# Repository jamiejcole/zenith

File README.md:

# Zenith
An open source EOS controller based on [ETC Lighthack](https://github.com/ETCLabs/lighthack).
I built this to assist with lighting programming alongside an ETC Element 2, more specifically out of my hatred for solely using point-and-click to control my moving heads. Hopefully this project is of use to someone else too.

## Features
- 3 customisable rotary encoders (default to pan, tilt and zoom)
- 3 cherry MX blue switches to change the action of the corresponding encoder
- Go and stop/back cue buttons
- OLED screen showing current encoder settings and values

## Hardware
To build this, I used:
- 5x cherry MX blue switches
- 3x rotary encoders with pushbuttons
- 0.96 128x64 OLED screen
- Arduino UNO clone
- 3D printed housing and encoder wheels
- 4x M3 threaded inserts

## Notable challenges
Due to using an Arduino clone rather than a genuine one, the arduino had trouble communicating to the Element 2 via OSC over USB, which was a headache to troubleshoot. 
This was mitigated by exiting EOS and using a dodgy workaround to get to control panel and sideloading the Arduino serial drivers by using a USB drive. The comments section of [Nathan Butler's Lighthack](https://tinkering.home.blog/2019/02/19/lighthack-usb-encoder-wing-for-etc-element/) project helped significantly through the process of attempting to get this to work:

>> A couple of things to try:
– The usual driver for the knockoff arduino’s that I’ve used was available at https://learn.sparkfun.com/tutorials/how-to-install-ch340-drivers/all#drivers-if-you-need-them. I downloaded the windows driver from there, put it on a USB, logged into the desk in admin mode, and was able to open the USB drive and just install it.
– Similarly, you could try installing the Arduino software on the ETC desk too, which includes some drivers as part of it’s install.
– Whilst I’m guessing that you’re using the same USB cable at the desk as you did to upload the firmware to the arduino, just in case you are not, try a different USB cable. I have had some funny issues which turned out to be an intermittently faulty cable
Hope that helps!

>> Element 2 CH340 Driver install
> Any update on this? I have a win7 element 2 console and my arduino uno clone is not being recognised at all in diagnostics page. It's using the CH340 chipset, really struggling to get this to work. Is there any way i can install the drivers onto the console?

Update on this, was able to install the correct drivers by:
- loading into the console ECU,
- spamming shift to open the sticky keys menu
- clicking the hyperlink on the prompt to open control panel
- open device manager from control panel
- find the COM port for the Arduino 
- insert usb with extracted .zip folder for windows 7 CH340 drivers, downloaded from [this page](https://www.wch-ic.com/downloads/CH341SER_ZIP.html)
- click update drivers 
- select update from local file
- find extracted driver folder on USB
- install drivers
- exit out of all windows and launch EOS primary
- COM4 port is now recognised and can talk to Arduino via OSC over USB

## Wiring
Here was my 'circuit diagram' for the build.

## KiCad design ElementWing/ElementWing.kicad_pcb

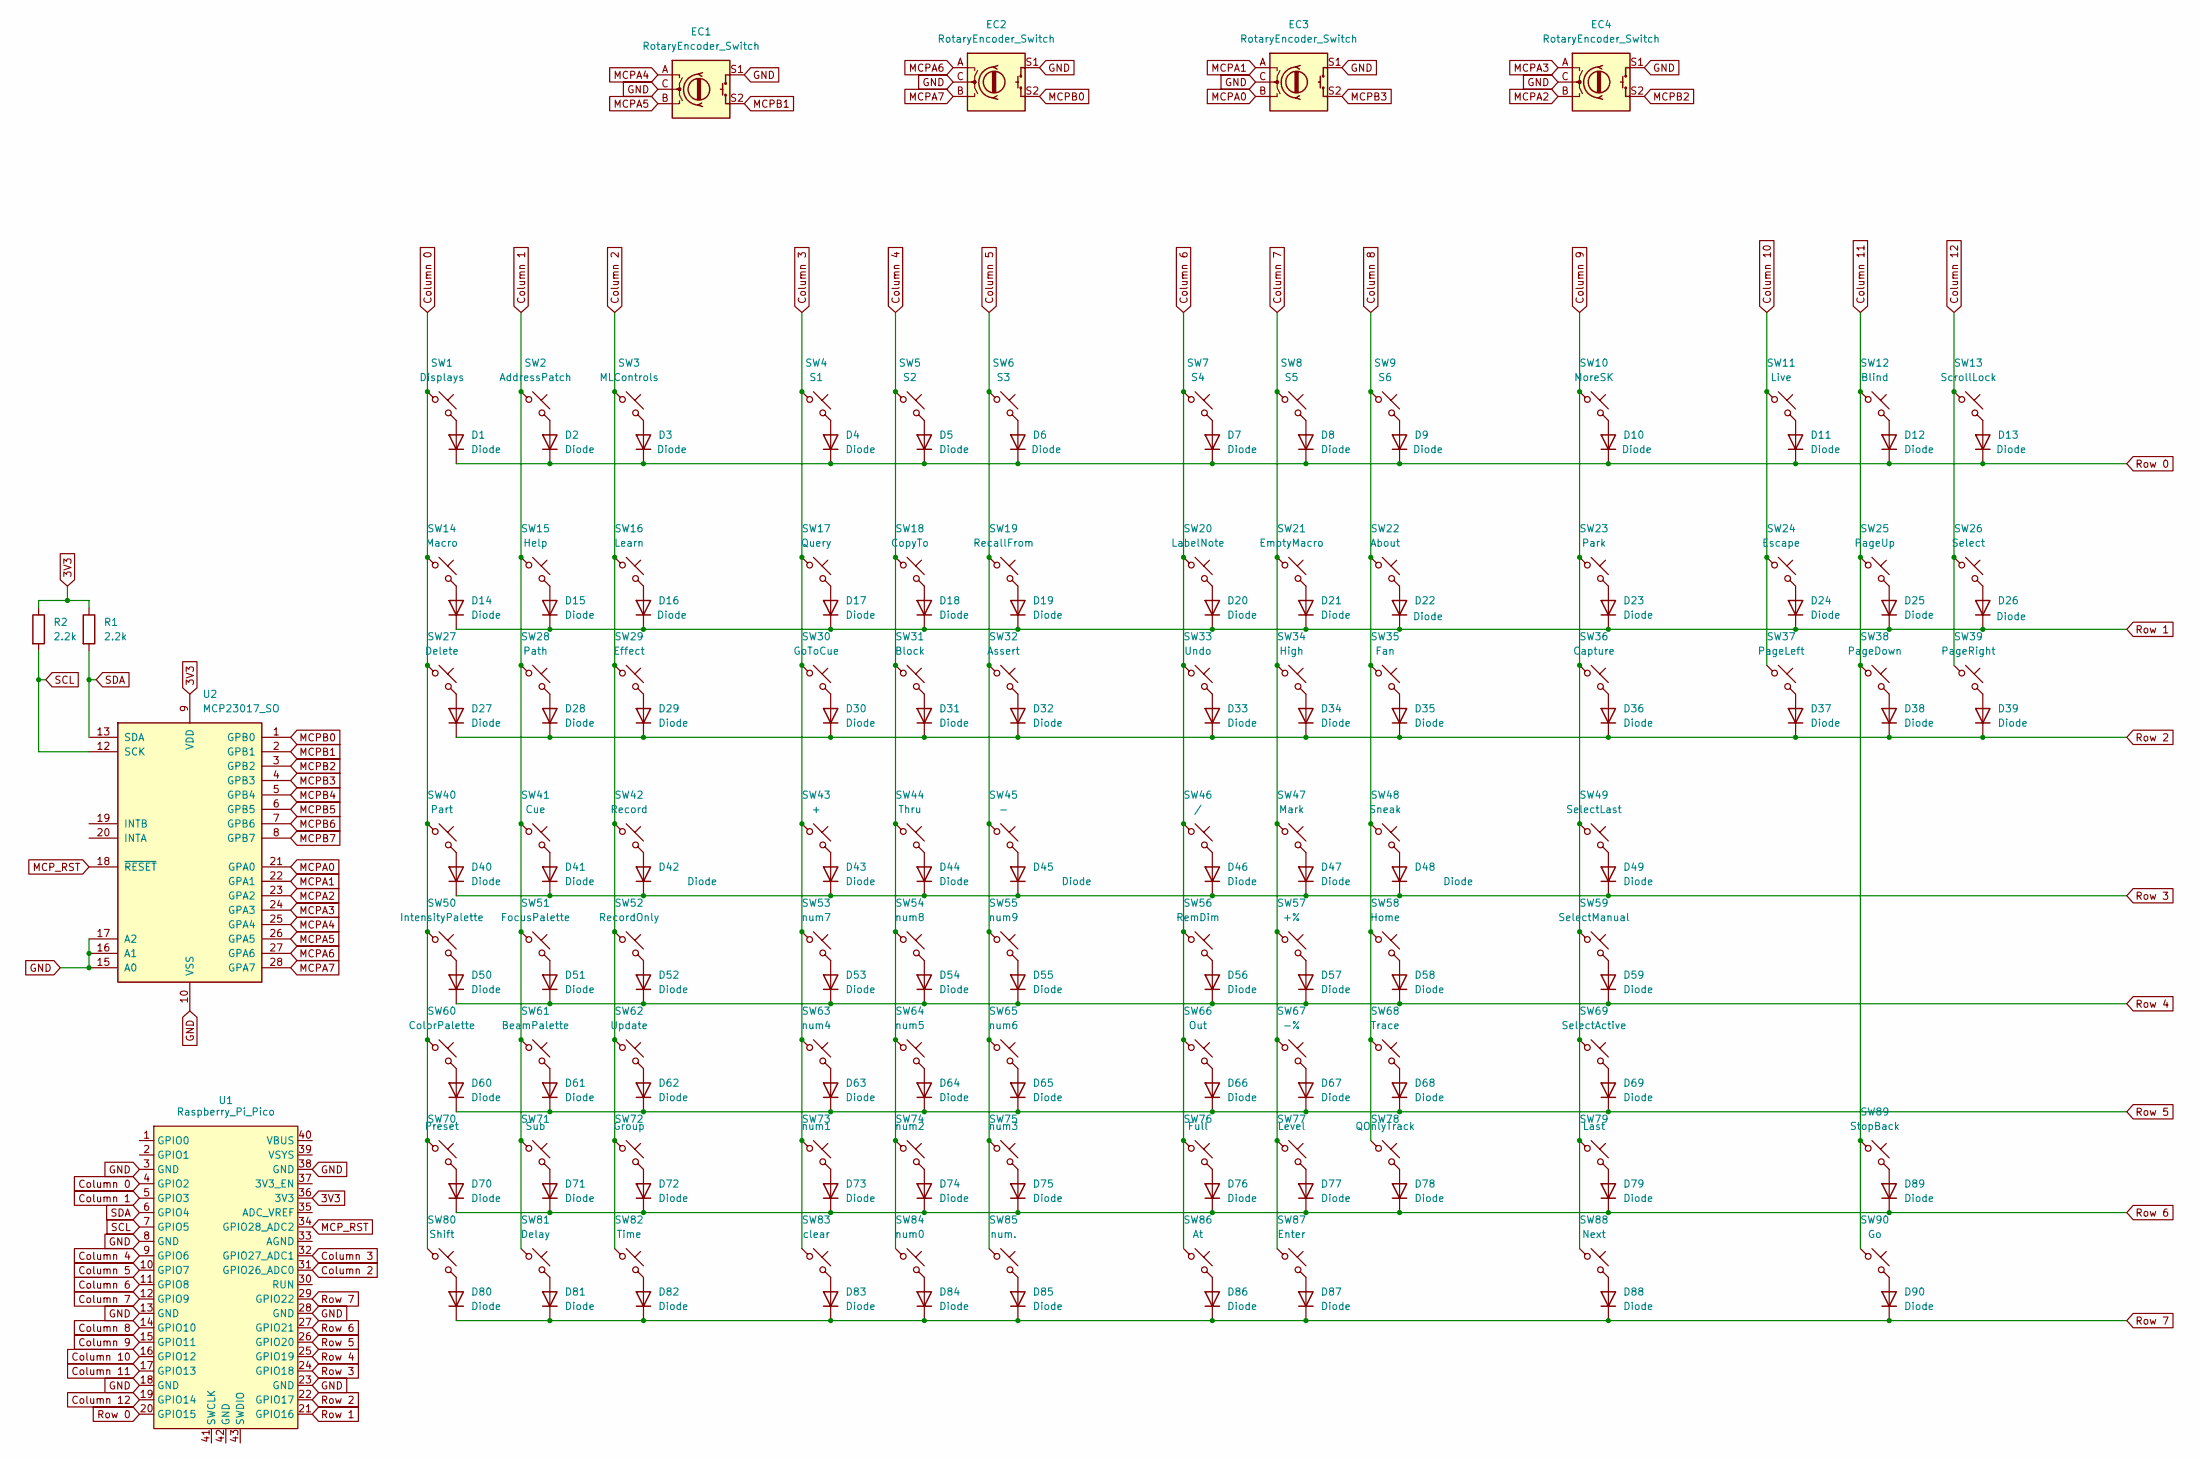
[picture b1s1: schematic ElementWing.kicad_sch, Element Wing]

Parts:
D1, D2, D3, D4, D5, D6, D7, D8, D9, D10, D11, D12, D13, D14, D15, D16, D17, D18, D19, D20, D21, D22, D23, D24, D25, D26, D27, D28, D29, D30, D31, D32, D33, D34, D35, D36, D37, D38, D39, D40, D41, D42, D43, D44, D45, D46, D47, D48, D49, D50, D51, D52, D53, D54, D55, D56, D57, D58, D59, D60, D61, D62, D63, D64, D65, D66, D67, D68, D69, D70, D71, D72, D73, D74, D75, D76, D77, D78, D79, D80, D81, D82, D83, D84, D85, D86, D87, D88, D89, D90: Diode; Diode_DO-35
EC1, EC2, EC3, EC4: RotaryEncoder_Switch; RotaryEncoder_Alps_EC11E-Switch_Vertical_H20mm
R1, R2: 2.2k; R_Axial_DIN0207_L6.3mm_D2.5mm_P10.16mm_Horizontal
SW1: Displays; MX_PCB_1.00u
SW2: AddressPatch; MX_PCB_1.00u
SW3: MLControls; MX_PCB_1.00u
SW4: S1; MX_PCB_1.00u
SW5: S2; MX_PCB_1.00u
SW6: S3; MX_PCB_1.00u
SW7: S4; MX_PCB_1.00u
SW8: S5; MX_PCB_1.00u
SW9: S6; MX_PCB_1.00u
SW10: MoreSK; MX_PCB_1.00u
SW11: Live; MX_PCB_1.00u
SW12: Blind; MX_PCB_1.00u
SW13: ScrollLock; MX_PCB_1.00u
SW14: Macro; MX_PCB_1.00u
SW15: Help; MX_PCB_1.00u
SW16: Learn; MX_PCB_1.00u
SW17: Query; MX_PCB_1.00u
SW18: CopyTo; MX_PCB_1.00u
SW19: RecallFrom; MX_PCB_1.00u
SW20: LabelNote; MX_PCB_1.00u
SW21: EmptyMacro; MX_PCB_1.00u
SW22: About; MX_PCB_1.00u
SW23: Park; MX_PCB_1.00u
SW24: Escape; MX_PCB_1.00u
SW25: PageUp; MX_PCB_1.00u
SW26: Select; MX_PCB_1.00u
SW27: Delete; MX_PCB_1.00u
SW28: Path; MX_PCB_1.00u
SW29: Effect; MX_PCB_1.00u
SW30: GoToCue; MX_PCB_1.00u
SW31: Block; MX_PCB_1.00u
SW32: Assert; MX_PCB_1.00u
SW33: Undo; MX_PCB_1.00u
SW34: High; MX_PCB_1.00u
SW35: Fan; MX_PCB_1.00u
SW36: Capture; MX_PCB_1.00u
SW37: PageLeft; MX_PCB_1.00u
SW38: PageDown; MX_PCB_1.00u
SW39: PageRight; MX_PCB_1.00u
SW40: Part; MX_PCB_1.00u
SW41: Cue; MX_PCB_1.00u
SW42: Record; MX_PCB_1.00u
SW43: +; MX_PCB_1.00u
SW44: Thru; MX_PCB_1.00u
SW45: -; MX_PCB_1.00u
SW46: /; MX_PCB_1.00u
SW47: Mark; MX_PCB_1.00u
SW48: Sneak; MX_PCB_1.00u
SW49: SelectLast; MX_PCB_1.00u
SW50: IntensityPalette; MX_PCB_1.00u
SW51: FocusPalette; MX_PCB_1.00u
SW52: RecordOnly; MX_PCB_1.00u
SW53: num7; MX_PCB_1.00u
SW54: num8; MX_PCB_1.00u
SW55: num9; MX_PCB_1.00u
SW56: RemDim; MX_PCB_1.00u
SW57: +%; MX_PCB_1.00u
SW58: Home; MX_PCB_1.00u
SW59: SelectManual; MX_PCB_1.00u
SW60: ColorPalette; MX_PCB_1.00u
SW61: BeamPalette; MX_PCB_1.00u
SW62: Update; MX_PCB_1.00u
SW63: num4; MX_PCB_1.00u
SW64: num5; MX_PCB_1.00u
SW65: num6; MX_PCB_1.00u
SW66: Out; MX_PCB_1.00u
SW67: -%; MX_PCB_1.00u
SW68: Trace; MX_PCB_1.00u
SW69: SelectActive; MX_PCB_1.00u
SW70: Preset; MX_PCB_1.00u
SW71: Sub; MX_PCB_1.00u
SW72: Group; MX_PCB_1.00u
SW73: num1; MX_PCB_1.00u
SW74: num2; MX_PCB_1.00u
SW75: num3; MX_PCB_1.00u
SW76: Full; MX_PCB_1.00u
SW77: Level; MX_PCB_1.00u
SW78: QOnlyTrack; MX_PCB_1.00u
SW79: Last; MX_PCB_1.00u
SW80: Shift; MX_PCB_1.00u
SW81: Delay; MX_PCB_1.00u
SW82: Time; MX_PCB_1.00u
SW83: clear; MX_PCB_1.00u
SW84: num0; MX_PCB_1.00u
SW85: num.; MX_PCB_1.00u
SW86: At; MX_PCB_1.00u
SW87: Enter; MX_PCB_1.00u
SW88: Next; MX_PCB_1.00u
SW89: StopBack; MX_PCB_1.00u
SW90: Go; MX_PCB_1.00u
U1: Raspberry_Pi_Pico
U2: MCP23017_SO; SOIC-28W_7.5x17.9mm_P1.27mm

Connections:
3V3: R1.1, R2.1, U1.36 (3V3), U2.9 (VDD)
Column 0: SW1.1, SW14.1, SW27.1, SW40.1, SW50.1, SW60.1, SW70.1, SW80.1, U1.4 (GPIO2)
Column 1: SW2.1, SW15.1, SW28.1, SW41.1, SW51.1, SW61.1, SW71.1, SW81.1, U1.5 (GPIO3)
Column 2: SW3.1, SW16.1, SW29.1, SW42.1, SW52.1, SW62.1, SW72.1, SW82.1, U1.31 (GPIO26_ADC0)
Column 3: SW4.1, SW17.1, SW30.1, SW43.1, SW53.1, SW63.1, SW73.1, SW83.1, U1.32 (GPIO27_ADC1)
Column 4: SW5.1, SW18.1, SW31.1, SW44.1, SW54.1, SW64.1, SW74.1, SW84.1, U1.9 (GPIO6)
Column 5: SW6.1, SW19.1, SW32.1, SW45.1, SW55.1, SW65.1, SW75.1, SW85.1, U1.10 (GPIO7)
Column 6: SW7.1, SW20.1, SW33.1, SW46.1, SW56.1, SW66.1, SW76.1, SW86.1, U1.11 (GPIO8)
Column 7: SW8.1, SW21.1, SW34.1, SW47.1, SW57.1, SW67.1, SW77.1, SW87.1, U1.12 (GPIO9)
Column 8: SW9.1, SW22.1, SW35.1, SW48.1, SW58.1, SW68.1, SW78.1, U1.14 (GPIO10)
Column 9: SW10.1, SW23.1, SW36.1, SW49.1, SW59.1, SW69.1, SW79.1, SW88.1, U1.15 (GPIO11)
Column 10: SW11.1, SW24.1, SW37.1, U1.16 (GPIO12)
Column 11: SW12.1, SW25.1, SW38.1, SW89.1, SW90.1, U1.17 (GPIO13)
Column 12: SW13.1, SW26.1, SW39.1, U1.19 (GPIO14)
GND: EC1.C, EC1.S1, EC2.C, EC2.S1, EC3.C, EC3.S1, EC4.C, EC4.S1, U1.3 (GND), U1.8 (GND), U1.13 (GND), U1.18 (GND), U1.23 (GND), U1.28 (GND), U1.38 (GND), U2.10 (VSS), U2.15 (A0), U2.16 (A1), U2.17 (A2)
MCPA0: EC3.B, U2.21 (GPA0)
MCPA1: EC3.A, U2.22 (GPA1)
MCPA2: EC4.B, U2.23 (GPA2)
MCPA3: EC4.A, U2.24 (GPA3)
MCPA4: EC1.A, U2.25 (GPA4)
MCPA5: EC1.B, U2.26 (GPA5)
MCPA6: EC2.A, U2.27 (GPA6)
MCPA7: EC2.B, U2.28 (GPA7)
MCPB0: EC2.S2, U2.1 (GPB0)
MCPB1: EC1.S2, U2.2 (GPB1)
MCPB2: EC4.S2, U2.3 (GPB2)
MCPB3: EC3.S2, U2.4 (GPB3)
MCPB4: U2.5 (GPB4)
MCPB5: U2.6 (GPB5)
MCPB6: U2.7 (GPB6)
MCPB7: U2.8 (GPB7)
MCP_RST: U1.34 (GPIO28_ADC2), U2.18 (~RESET)
unnamed: D1.2 (A), SW1.2
unnamed: D2.2 (A), SW2.2
unnamed: D3.2 (A), SW3.2
unnamed: D4.2 (A), SW4.2
unnamed: D5.2 (A), SW5.2
unnamed: D6.2 (A), SW6.2
unnamed: D7.2 (A), SW7.2
unnamed: D8.2 (A), SW8.2
unnamed: D9.2 (A), SW9.2
unnamed: D10.2 (A), SW10.2
unnamed: D11.2 (A), SW11.2
unnamed: D12.2 (A), SW12.2
unnamed: D13.2 (A), SW13.2
unnamed: D14.2 (A), SW14.2
unnamed: D15.2 (A), SW15.2
unnamed: D16.2 (A), SW16.2
unnamed: D17.2 (A), SW17.2
unnamed: D18.2 (A), SW18.2
unnamed: D19.2 (A), SW19.2
unnamed: D20.2 (A), SW20.2
unnamed: D21.2 (A), SW21.2
unnamed: D22.2 (A), SW22.2
unnamed: D23.2 (A), SW23.2
unnamed: D24.2 (A), SW24.2
unnamed: D25.2 (A), SW25.2
unnamed: D26.2 (A), SW26.2
unnamed: D27.2 (A), SW27.2
unnamed: D28.2 (A), SW28.2
unnamed: D29.2 (A), SW29.2
unnamed: D30.2 (A), SW30.2
unnamed: D31.2 (A), SW31.2
unnamed: D32.2 (A), SW32.2
unnamed: D33.2 (A), SW33.2
unnamed: D34.2 (A), SW34.2
unnamed: D35.2 (A), SW35.2
unnamed: D36.2 (A), SW36.2
unnamed: D37.2 (A), SW37.2
unnamed: D38.2 (A), SW38.2
unnamed: D39.2 (A), SW39.2
unnamed: D40.2 (A), SW40.2
unnamed: D41.2 (A), SW41.2
unnamed: D42.2 (A), SW42.2
unnamed: D43.2 (A), SW43.2
unnamed: D44.2 (A), SW44.2
unnamed: D45.2 (A), SW45.2
unnamed: D46.2 (A), SW46.2
unnamed: D47.2 (A), SW47.2
unnamed: D48.2 (A), SW48.2
unnamed: D49.2 (A), SW49.2
unnamed: D50.2 (A), SW50.2
unnamed: D51.2 (A), SW51.2
unnamed: D52.2 (A), SW52.2
unnamed: D53.2 (A), SW53.2
unnamed: D54.2 (A), SW54.2
unnamed: D55.2 (A), SW55.2
unnamed: D56.2 (A), SW56.2
unnamed: D57.2 (A), SW57.2
unnamed: D58.2 (A), SW58.2
unnamed: D59.2 (A), SW59.2
unnamed: D60.2 (A), SW60.2
unnamed: D61.2 (A), SW61.2
unnamed: D62.2 (A), SW62.2
unnamed: D63.2 (A), SW63.2
unnamed: D64.2 (A), SW64.2
unnamed: D65.2 (A), SW65.2
unnamed: D66.2 (A), SW66.2
unnamed: D67.2 (A), SW67.2
unnamed: D68.2 (A), SW68.2
unnamed: D69.2 (A), SW69.2
unnamed: D70.2 (A), SW70.2
unnamed: D71.2 (A), SW71.2
unnamed: D72.2 (A), SW72.2
unnamed: D73.2 (A), SW73.2
unnamed: D74.2 (A), SW74.2
unnamed: D75.2 (A), SW75.2
unnamed: D76.2 (A), SW76.2
unnamed: D77.2 (A), SW77.2
unnamed: D78.2 (A), SW78.2
unnamed: D79.2 (A), SW79.2
unnamed: D80.2 (A), SW80.2
unnamed: D81.2 (A), SW81.2
unnamed: D82.2 (A), SW82.2
unnamed: D83.2 (A), SW83.2
unnamed: D84.2 (A), SW84.2
unnamed: D85.2 (A), SW85.2
unnamed: D86.2 (A), SW86.2
unnamed: D87.2 (A), SW87.2
unnamed: D88.2 (A), SW88.2
unnamed: D89.2 (A), SW89.2
unnamed: D90.2 (A), SW90.2
Row 0: D1.1 (K), D2.1 (K), D3.1 (K), D4.1 (K), D5.1 (K), D6.1 (K), D7.1 (K), D8.1 (K), D9.1 (K), D10.1 (K), D11.1 (K), D12.1 (K), D13.1 (K), U1.20 (GPIO15)
Row 1: D14.1 (K), D15.1 (K), D16.1 (K), D17.1 (K), D18.1 (K), D19.1 (K), D20.1 (K), D21.1 (K), D22.1 (K), D23.1 (K), D24.1 (K), D25.1 (K), D26.1 (K), U1.21 (GPIO16)
Row 2: D27.1 (K), D28.1 (K), D29.1 (K), D30.1 (K), D31.1 (K), D32.1 (K), D33.1 (K), D34.1 (K), D35.1 (K), D36.1 (K), D37.1 (K), D38.1 (K), D39.1 (K), U1.22 (GPIO17)
Row 3: D40.1 (K), D41.1 (K), D42.1 (K), D43.1 (K), D44.1 (K), D45.1 (K), D46.1 (K), D47.1 (K), D48.1 (K), D49.1 (K), U1.24 (GPIO18)
Row 4: D50.1 (K), D51.1 (K), D52.1 (K), D53.1 (K), D54.1 (K), D55.1 (K), D56.1 (K), D57.1 (K), D58.1 (K), D59.1 (K), U1.25 (GPIO19)
Row 5: D60.1 (K), D61.1 (K), D62.1 (K), D63.1 (K), D64.1 (K), D65.1 (K), D66.1 (K), D67.1 (K), D68.1 (K), D69.1 (K), U1.26 (GPIO20)
Row 6: D70.1 (K), D71.1 (K), D72.1 (K), D73.1 (K), D74.1 (K), D75.1 (K), D76.1 (K), D77.1 (K), D78.1 (K), D79.1 (K), D89.1 (K), U1.27 (GPIO21)
Row 7: D80.1 (K), D81.1 (K), D82.1 (K), D83.1 (K), D84.1 (K), D85.1 (K), D86.1 (K), D87.1 (K), D88.1 (K), D90.1 (K), U1.29 (GPIO22)
SCL: R2.2, U1.7 (GPIO5), U2.12 (SCK)
SDA: R1.2, U1.6 (GPIO4), U2.13 (SDA)

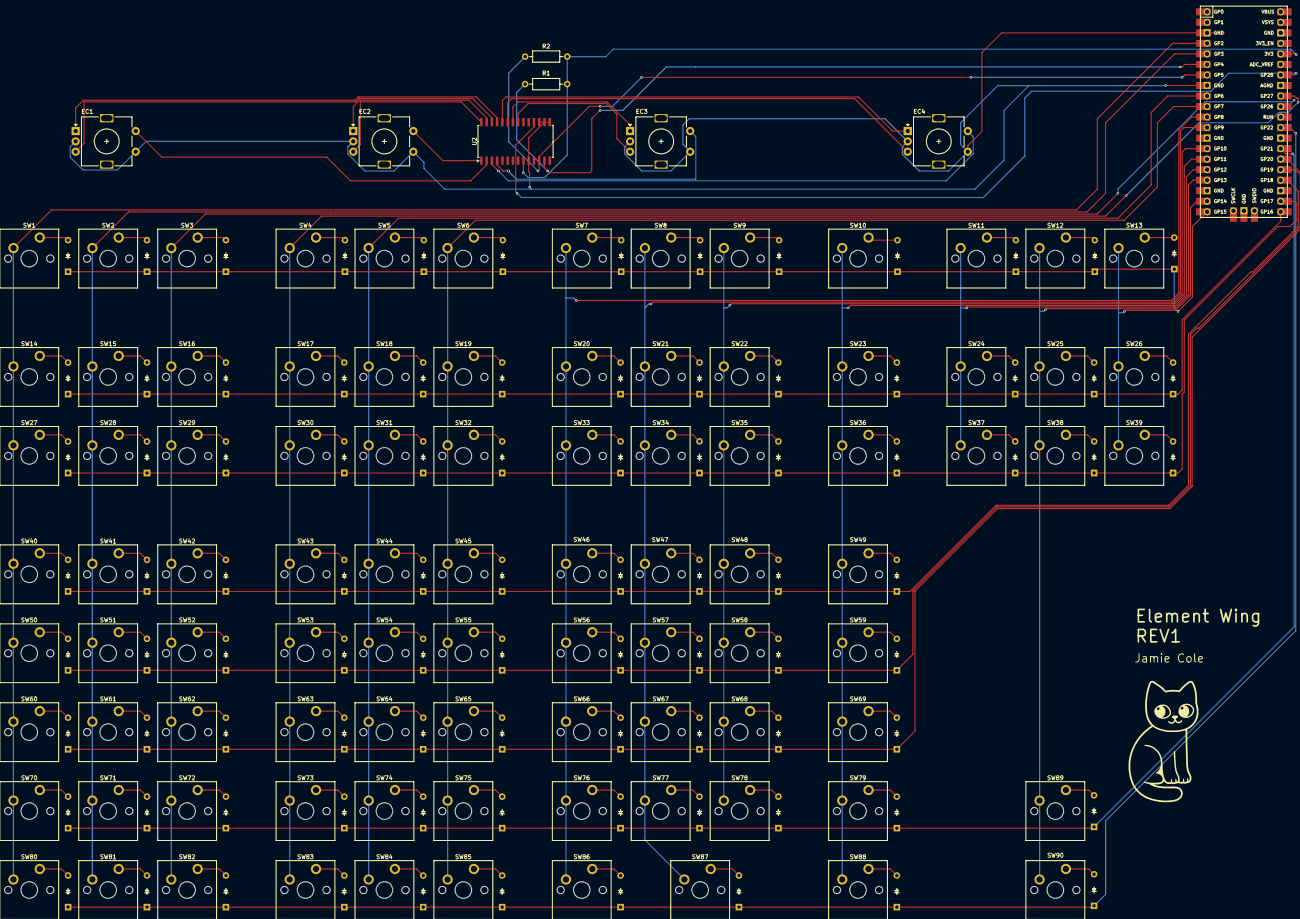
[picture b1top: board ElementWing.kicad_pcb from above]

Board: 2 copper layers, 188 parts (0 on the bottom side), 128 nets.

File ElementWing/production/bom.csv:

Designator,Footprint,Quantity,Value,LCSC Part #
"D1, D10, D11, D12, D13, D14, D15, D16, D17, D18, D19, D2, D20, D21, D22, D23, D24, D25, D26, D27, D28, D29, D3, D30, D31, D32, D33, D34, D35, D36, D37, D38, D39, D4, D40, D41, D42, D43, D44, D45, D46, D47, D48, D49, D5, D50, D51, D52, D53, D54, D55, D56, D57, D58, D59, D6, D60, D61, D62, D63, D64, D65, D66, D67, D68, D69, D7, D70, D71, D72, D73, D74, D75, D76, D77, D78, D79, D8, D80, D81, D82, D83, D84, D85, D86, D87, D88, D89, D9, D90",Diode_DO-35,90,Diode,
SW1,MX_PCB_1.00u,1,Displays,
SW10,MX_PCB_1.00u,1,MoreSK,
SW11,MX_PCB_1.00u,1,Live,
SW12,MX_PCB_1.00u,1,Blind,
SW13,MX_PCB_1.00u,1,ScrollLock,
SW14,MX_PCB_1.00u,1,Macro,
SW15,MX_PCB_1.00u,1,Help,
SW16,MX_PCB_1.00u,1,Learn,
SW17,MX_PCB_1.00u,1,Query,
SW18,MX_PCB_1.00u,1,CopyTo,
SW19,MX_PCB_1.00u,1,RecallFrom,
SW2,MX_PCB_1.00u,1,AddressPatch,
SW20,MX_PCB_1.00u,1,LabelNote,
SW21,MX_PCB_1.00u,1,EmptyMacro,
SW22,MX_PCB_1.00u,1,About,
SW23,MX_PCB_1.00u,1,Park,
SW24,MX_PCB_1.00u,1,Escape,
SW25,MX_PCB_1.00u,1,PageUp,
SW26,MX_PCB_1.00u,1,Select,
SW27,MX_PCB_1.00u,1,Delete,
SW28,MX_PCB_1.00u,1,Path,
SW29,MX_PCB_1.00u,1,Effect,
SW3,MX_PCB_1.00u,1,MLControls,
SW30,MX_PCB_1.00u,1,GoToCue,
SW31,MX_PCB_1.00u,1,Block,
SW32,MX_PCB_1.00u,1,Assert,
SW33,MX_PCB_1.00u,1,Undo,
SW34,MX_PCB_1.00u,1,High,
SW35,MX_PCB_1.00u,1,Fan,
SW36,MX_PCB_1.00u,1,Capture,
SW37,MX_PCB_1.00u,1,PageLeft,
SW38,MX_PCB_1.00u,1,PageDown,
SW39,MX_PCB_1.00u,1,PageRight,
SW4,MX_PCB_1.00u,1,S1,
SW40,MX_PCB_1.00u,1,Part,
SW41,MX_PCB_1.00u,1,Cue,
SW42,MX_PCB_1.00u,1,Record,
SW43,MX_PCB_1.00u,1,+,
SW44,MX_PCB_1.00u,1,Thru,
SW45,MX_PCB_1.00u,1,-,
SW46,MX_PCB_1.00u,1,/,
SW47,MX_PCB_1.00u,1,Mark,
SW48,MX_PCB_1.00u,1,Sneak,
SW49,MX_PCB_1.00u,1,SelectLast,
SW5,MX_PCB_1.00u,1,S2,
SW50,MX_PCB_1.00u,1,IntensityPalette,
SW51,MX_PCB_1.00u,1,FocusPalette,
SW52,MX_PCB_1.00u,1,RecordOnly,
SW53,MX_PCB_1.00u,1,num7,
SW54,MX_PCB_1.00u,1,num8,
SW55,MX_PCB_1.00u,1,num9,
SW56,MX_PCB_1.00u,1,RemDim,
SW57,MX_PCB_1.00u,1,+%,
SW58,MX_PCB_1.00u,1,Home,
SW59,MX_PCB_1.00u,1,SelectManual,
SW6,MX_PCB_1.00u,1,S3,
SW60,MX_PCB_1.00u,1,ColorPalette,
SW61,MX_PCB_1.00u,1,BeamPalette,
SW62,MX_PCB_1.00u,1,Update,
SW63,MX_PCB_1.00u,1,num4,
SW64,MX_PCB_1.00u,1,num5,
SW65,MX_PCB_1.00u,1,num6,
SW66,MX_PCB_1.00u,1,Out,
SW67,MX_PCB_1.00u,1,-%,
SW68,MX_PCB_1.00u,1,Trace,
SW69,MX_PCB_1.00u,1,SelectActive,
SW7,MX_PCB_1.00u,1,S4,
SW70,MX_PCB_1.00u,1,Preset,
SW71,MX_PCB_1.00u,1,Sub,
SW72,MX_PCB_1.00u,1,Group,
SW73,MX_PCB_1.00u,1,num1,
SW74,MX_PCB_1.00u,1,num2,
SW75,MX_PCB_1.00u,1,num3,
SW76,MX_PCB_1.00u,1,Full,
SW77,MX_PCB_1.00u,1,Level,
SW78,MX_PCB_1.00u,1,QOnlyTrack,
SW79,MX_PCB_1.00u,1,Last,
SW8,MX_PCB_1.00u,1,S5,
SW80,MX_PCB_1.00u,1,Shift,
SW81,MX_PCB_1.00u,1,Delay,
SW82,MX_PCB_1.00u,1,Time,
SW83,MX_PCB_1.00u,1,clear,
SW84,MX_PCB_1.00u,1,num0,
SW85,MX_PCB_1.00u,1,num.,
SW86,MX_PCB_1.00u,1,At,
SW87,MX_PCB_1.00u,1,Enter,
SW88,MX_PCB_1.00u,1,Next,
SW89,MX_PCB_1.00u,1,StopBack,
SW9,MX_PCB_1.00u,1,S6,
SW90,MX_PCB_1.00u,1,Go,
U1,Raspberry_Pi_Pico,1,Raspberry_Pi_Pico,

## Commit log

2023-10-27 Initial Upload
2023-12-09 files
2024-05-25 added model and pics
2024-05-25 Added a README
2024-10-10 starting mk2
2024-11-01 added mk2 test code
2024-11-01 got all wheels working
2024-11-03 MK2 v1.0 Complete
2024-11-26 Added MK2.5 Initial Files
2024-11-27 fixed mk2.5 ish
2024-12-16 added pcb files
2024-12-16 added drawings
2024-12-16 updaye
2024-12-16 ordered pcb
2025-01-04 moved element wing to separate repo
